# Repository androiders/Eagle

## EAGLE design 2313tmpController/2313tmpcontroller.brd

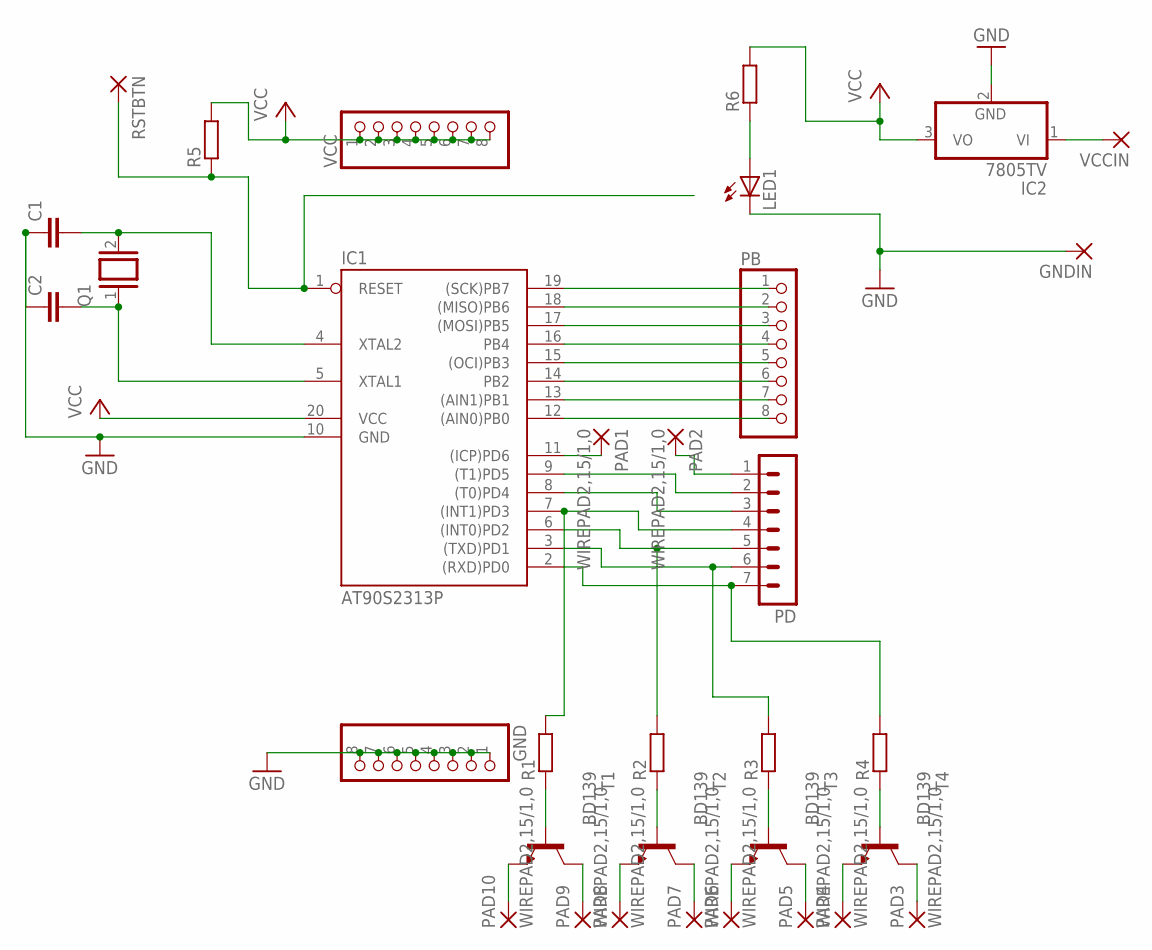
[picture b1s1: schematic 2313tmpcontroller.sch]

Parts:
C1, C2: C2,5-3; C2.5-3
GND: PINHD-1X8; 1X08
GNDIN: 2,54/0,8
IC1: AT90S2313P; DIL20
IC2: 7805TV; TO220V
LED1: LEDB153; Q62902-B153
PAD1, PAD2, PAD3, PAD4, PAD5, PAD6, PAD7, PAD8, PAD9, PAD10: WIREPAD2,15/1,0; 2,15/1,0
PB: PINHD-1X8; 1X08
PD: MA07-1
Q1: XTAL/S; QS
R1, R2, R3, R4, R5, R6: R-EU_0207/7; 0207/7
RSTBTN: 2,54/0,8
T1, T2, T3, T4: BD139; TO126
VCC: PINHD-1X8; 1X08
VCCIN: 2,54/0,8

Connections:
GND: C1.1, C2.1, GND.1, GND.2, GND.3, GND.4, GND.5, GND.6, GND.7, GND.8, GNDIN.1, IC1.10 (GND), IC2.2 (GND), LED1.K (C)
unnamed: IC1.12 ((AIN0)PB0), PB.8
unnamed: IC1.13 ((AIN1)PB1), PB.7
unnamed: IC1.14 (PB2), PB.6
unnamed: IC1.15 ((OCI)PB3), PB.5
unnamed: IC1.16 (PB4), PB.4
unnamed: IC1.17 ((MOSI)PB5), PB.3
unnamed: IC1.18 ((MISO)PB6), PB.2
unnamed: IC1.19 ((SCK)PB7), PB.1
unnamed: IC1.2 ((RXD)PD0), PD.7, R4.2
unnamed: IC1.3 ((TXD)PD1), PD.6, R3.2
unnamed: IC1.6 ((INT0)PD2), PD.5, R2.2
unnamed: IC1.7 ((INT1)PD3), PD.4, R1.2
unnamed: IC1.8 ((T0)PD4), PD.3
unnamed: IC1.9 ((T1)PD5), PD.2
unnamed: IC1.11 ((ICP)PD6), PAD1.1
unnamed: C2.2, IC1.5 (XTAL1), Q1.1
unnamed: C1.2, IC1.4 (XTAL2), Q1.2
unnamed: R1.1, T1.3 (B)
unnamed: IC1.1 (RESET), R5.1, RSTBTN.1
unnamed: R2.1, T2.3 (B)
unnamed: R3.1, T3.3 (B)
unnamed: R4.1, T4.3 (B)
unnamed: PAD10.1, T1.1 (E)
unnamed: PAD9.1, T1.2 (C)
unnamed: PAD8.1, T2.1 (E)
unnamed: PAD7.1, T2.2 (C)
unnamed: PAD6.1, T3.1 (E)
unnamed: PAD5.1, T3.2 (C)
unnamed: PAD4.1, T4.1 (E)
unnamed: PAD3.1, T4.2 (C)
unnamed: PAD2.1, PD.1
unnamed: LED1.A, R6.1
unnamed: IC2.1 (VI), VCCIN.1
VCC: IC1.20 (VCC), IC2.3 (VO), R5.2, R6.2, VCC.1, VCC.2, VCC.3, VCC.4, VCC.5, VCC.6, VCC.7, VCC.8

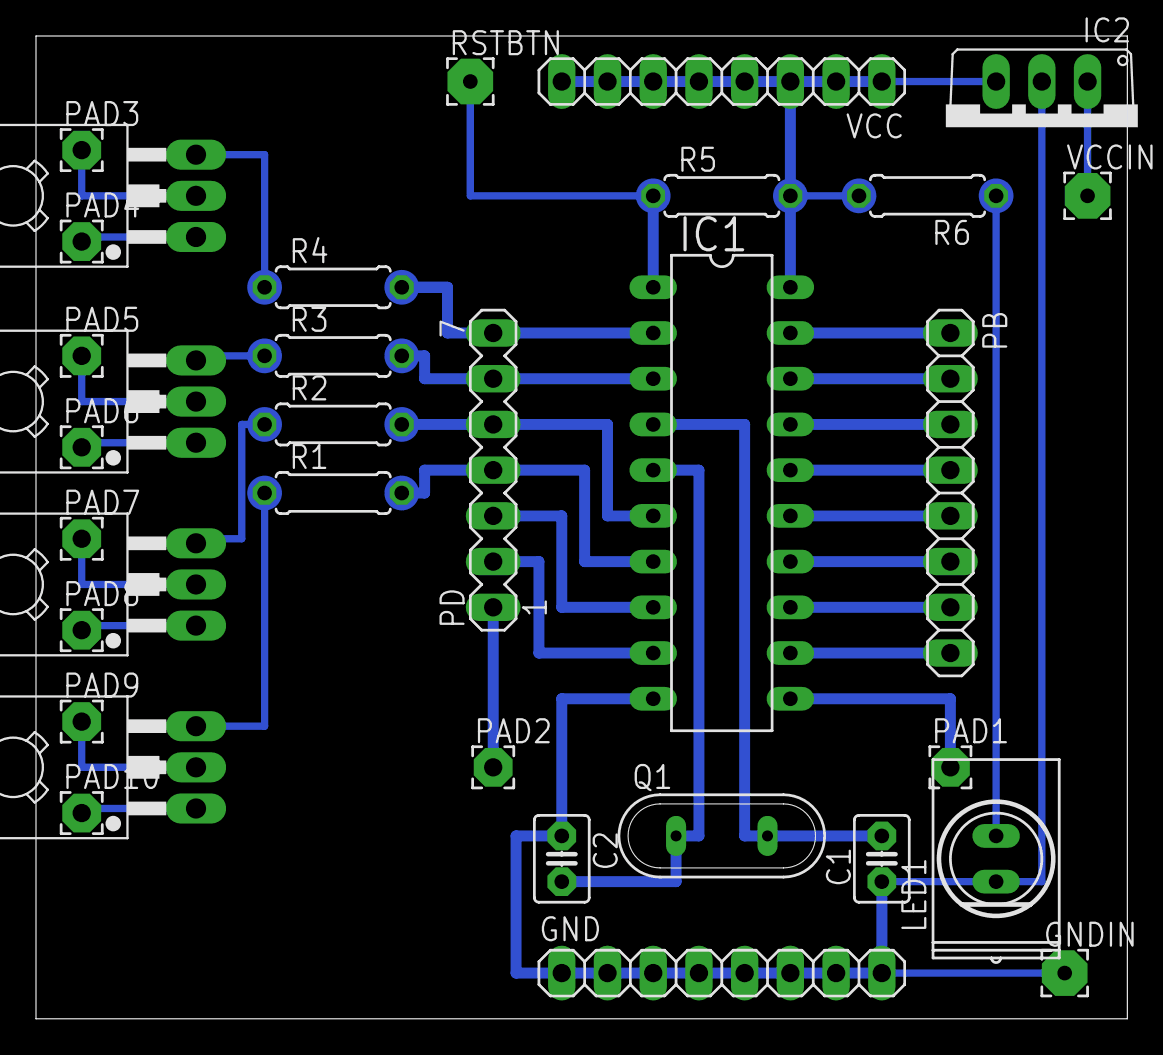
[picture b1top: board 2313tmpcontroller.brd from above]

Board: 2 copper layers, 60.6 x 54.6 mm, 33 parts (0 on the bottom side), 35 nets.

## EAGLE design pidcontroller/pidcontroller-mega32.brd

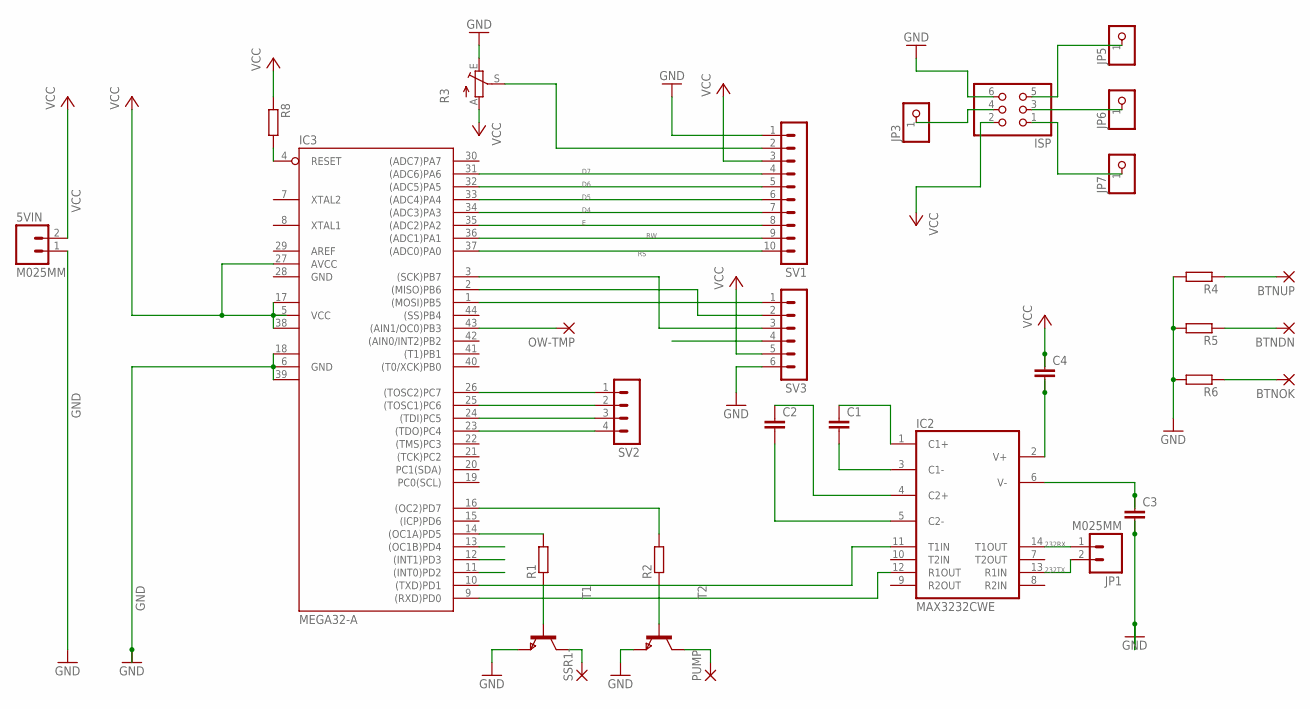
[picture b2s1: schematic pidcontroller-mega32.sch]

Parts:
5VIN: M025MM; SCREWTERMINAL-5MM-2
BTNDN: 2,15/1,0
BTNOK: 2,15/1,0
BTNUP: 2,15/1,0
C1, C2, C3, C4: C-EUC1206; C1206
IC2: MAX3232CWE; SO16L
IC3: MEGA32-A; TQFP44
ISP: PINHD-2X3; 2X03
JP1: M025MM; SCREWTERMINAL-5MM-2
JP3, JP5, JP6, JP7: PINHD-1X1; 1X01
OW-TMP: 2,15/1,0
PUMP: 2,15/1,0
R1, R2, R4, R5, R6, R8: R-EU_R0603; R0603
R3: TRIM_EU-LI10; LI10
SSR1-: 2,15/1,0
SV1: MA10-1
SV2: MA04-1
SV3: MA06-1
T1, T2: NPNSOT23; SOT-23

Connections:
232RX: IC2.14 (T1OUT), JP1.1
232TX: IC2.13 (R1IN), JP1.2
BTNDN: BTNDN.1, IC3.12 ((INT1)PD3), R5.1
BTNOK: BTNOK.1, IC3.11 ((INT0)PD2), R6.1
BTNUP: BTNUP.1, IC3.13 ((OC1B)PD4), R4.1
D4: IC3.34 ((ADC3)PA3), SV1.7
D5: IC3.33 ((ADC4)PA4), SV1.6
D6: IC3.32 ((ADC5)PA5), SV1.5
D7: IC3.31 ((ADC6)PA6), SV1.4
E: IC3.35 ((ADC2)PA2), SV1.8
GND: 5VIN.1, C3.2, IC2.15 (GND), IC3.6 (GND), IC3.18 (GND1), IC3.28 (GND), IC3.39 (GND2), ISP.6, R3.E, R4.2, R5.2, R6.2, SV1.1, SV3.6, T1.2 (E), T2.2 (E)
unnamed: IC3.3 ((SCK)PB7), SV3.3
unnamed: R1.1, T1.3 (B)
unnamed: R2.1, T2.3 (B)
unnamed: IC3.14 ((OC1A)PD5), R1.2
unnamed: C2.2, IC2.5 (C2-)
unnamed: C2.1, IC2.4 (C2+)
unnamed: C1.2, IC2.3 (C1-)
unnamed: C1.1, IC2.1 (C1+)
unnamed: C4.2, IC2.2 (V+)
unnamed: IC3.16 ((OC2)PD7), R2.2
unnamed: C3.1, IC2.6 (V-)
unnamed: IC2.11 (T1IN), IC3.10 ((TXD)PD1)
unnamed: IC2.12 (R1OUT), IC3.9 ((RXD)PD0)
unnamed: IC3.1 ((MOSI)PB5), SV3.1
unnamed: IC3.2 ((MISO)PB6), SV3.2
unnamed: IC3.43 ((AIN1/OC0)PB3), OW-TMP.1
unnamed: R3.S, SV1.2
unnamed: ISP.4, JP3.1
unnamed: SSR1-.1, T1.1 (C)
unnamed: PUMP.1, T2.1 (C)
unnamed: ISP.1, JP7.1
unnamed: ISP.3, JP6.1
unnamed: ISP.5, JP5.1
unnamed: IC3.26 ((TOSC2)PC7), SV2.1
unnamed: IC3.25 ((TOSC1)PC6), SV2.2
unnamed: IC3.24 ((TDI)PC5), SV2.3
unnamed: IC3.23 ((TDO)PC4), SV2.4
RESET: IC3.4 (RESET), R8.2, SV3.4
RS: IC3.37 ((ADC0)PA0), SV1.10
RW: IC3.36 ((ADC1)PA1), SV1.9
VCC: 5VIN.2, C4.1, IC2.16 (VCC), IC3.5 (VCC), IC3.17 (VCC1), IC3.27 (AVCC), IC3.38 (VCC2), ISP.2, R3.A, R8.1, SV1.3, SV3.5

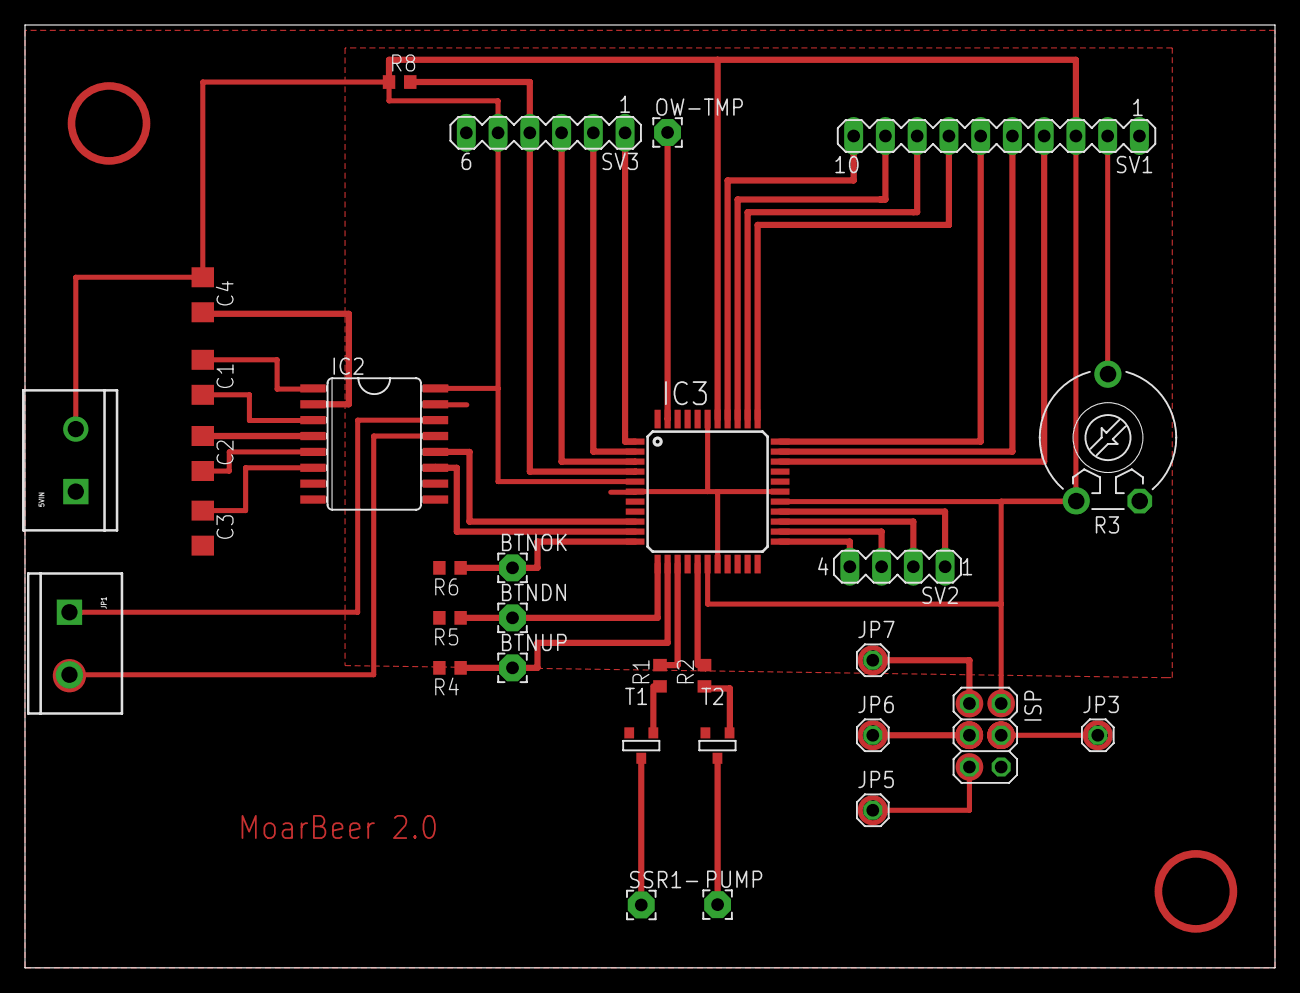
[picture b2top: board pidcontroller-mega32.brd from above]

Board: 2 copper layers, 100.0 x 75.4 mm, 31 parts (0 on the bottom side), 42 nets.

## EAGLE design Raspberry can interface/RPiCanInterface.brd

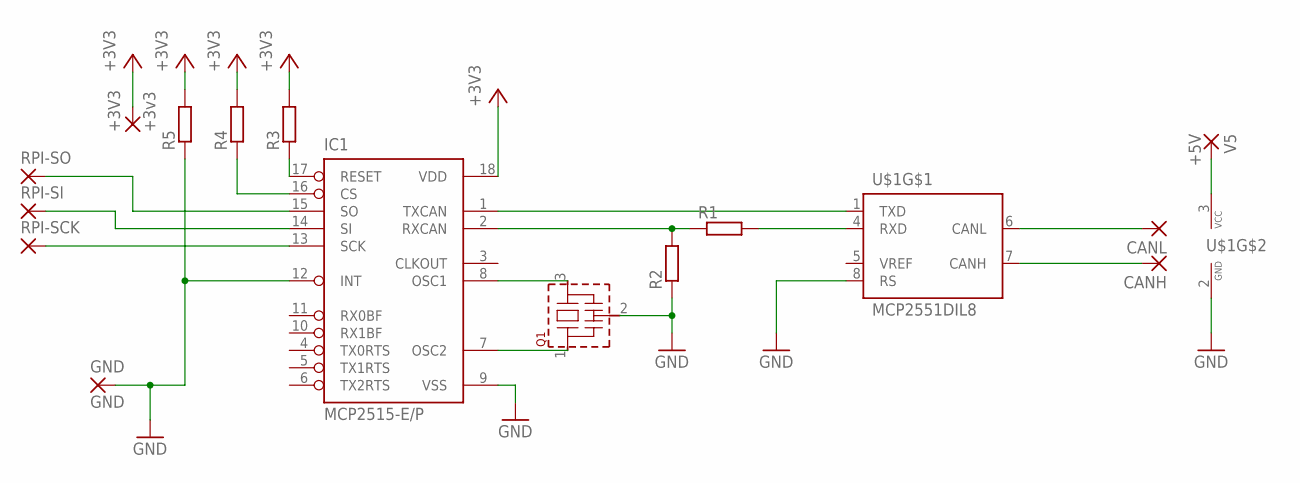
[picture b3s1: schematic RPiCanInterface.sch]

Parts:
+3V3: +3v3; 1,6/0,8
CANH: 1,6/0,8
CANL: 1,6/0,8
GND: GND; 1,6/0,8
IC1: MCP2515-E/P; DIL18
Q1: CSTLA_T
R1, R2, R3, R4, R5: R-EU_0207/7; 0207/7
RPI-SCK: 1,6/0,8
RPI-SI: 1,6/0,8
RPI-SO: 1,6/0,8
U$1: MCP2551DIL8; DIL08
V5: +5V; 1,6/0,8

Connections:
GND: GND.1, IC1.9 (VSS), IC1.12 (INT), Q1.2 (VSS), R2.1, R5.1, U$1.2 (GND), U$1.8 (RS)
unnamed: IC1.1 (TXCAN), U$1.1 (TXD)
unnamed: IC1.2 (RXCAN), R1.1, R2.2
unnamed: R1.2, U$1.4 (RXD)
unnamed: IC1.7 (OSC2), Q1.1
unnamed: IC1.8 (OSC1), Q1.3
unnamed: CANL.1, U$1.6 (CANL)
unnamed: CANH.1, U$1.7 (CANH)
unnamed: IC1.17 (RESET), R3.1
unnamed: IC1.16 (CS), R4.1
unnamed: IC1.15 (SO), RPI-SO.1
unnamed: IC1.14 (SI), RPI-SI.1
unnamed: IC1.13 (SCK), RPI-SCK.1
unnamed: U$1.3 (VCC), V5.1
VCC: +3V3.1, IC1.18 (VDD), R3.2, R4.2, R5.2

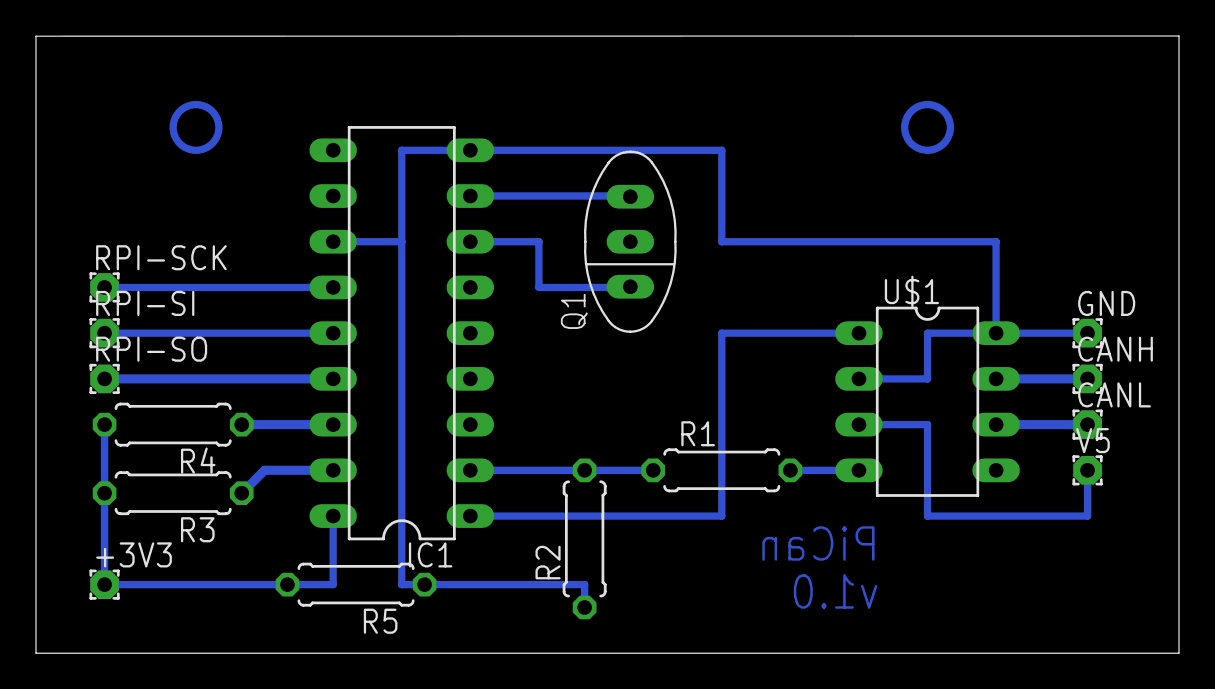
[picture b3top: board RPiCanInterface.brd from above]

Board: 2 copper layers, 63.5 x 34.3 mm, 16 parts (0 on the bottom side), 15 nets.

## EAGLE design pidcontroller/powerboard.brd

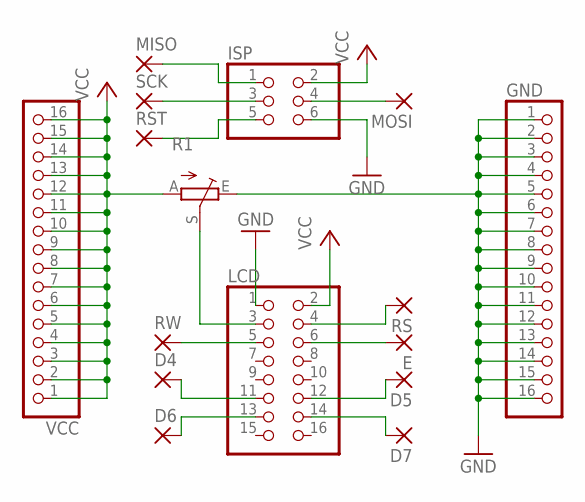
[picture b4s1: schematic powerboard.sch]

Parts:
D4, D5, D6, D7: 2,54/1,1
E: 2,54/1,1
GND: PINHD-1X16; 1X16
ISP: PINHD-2X3; 2X03
LCD: PINHD-2X8; 2X08
MISO: 2,54/1,1
MOSI: 2,54/1,1
R1: TRIM_EU-LI10; LI10
RS: 2,54/1,1
RST: 2,54/1,1
RW: 2,54/1,1
SCK: 2,54/1,1
VCC: PINHD-1X16; 1X16

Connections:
GND: GND.1, GND.2, GND.3, GND.4, GND.5, GND.6, GND.7, GND.8, GND.9, GND.10, GND.11, GND.12, GND.13, GND.14, GND.15, GND.16, ISP.6, LCD.1, R1.E
unnamed: LCD.4, RS.1
unnamed: LCD.5, RW.1
unnamed: ISP.1, MISO.1
unnamed: ISP.3, SCK.1
unnamed: ISP.5, RST.1
unnamed: ISP.4, MOSI.1
unnamed: E.1, LCD.6
unnamed: D4.1, LCD.11
unnamed: D5.1, LCD.12
unnamed: D6.1, LCD.13
unnamed: D7.1, LCD.14
unnamed: LCD.3, R1.S
VCC: ISP.2, LCD.2, R1.A, VCC.1, VCC.2, VCC.3, VCC.4, VCC.5, VCC.6, VCC.7, VCC.8, VCC.9, VCC.10, VCC.11, VCC.12, VCC.13, VCC.14, VCC.15, VCC.16

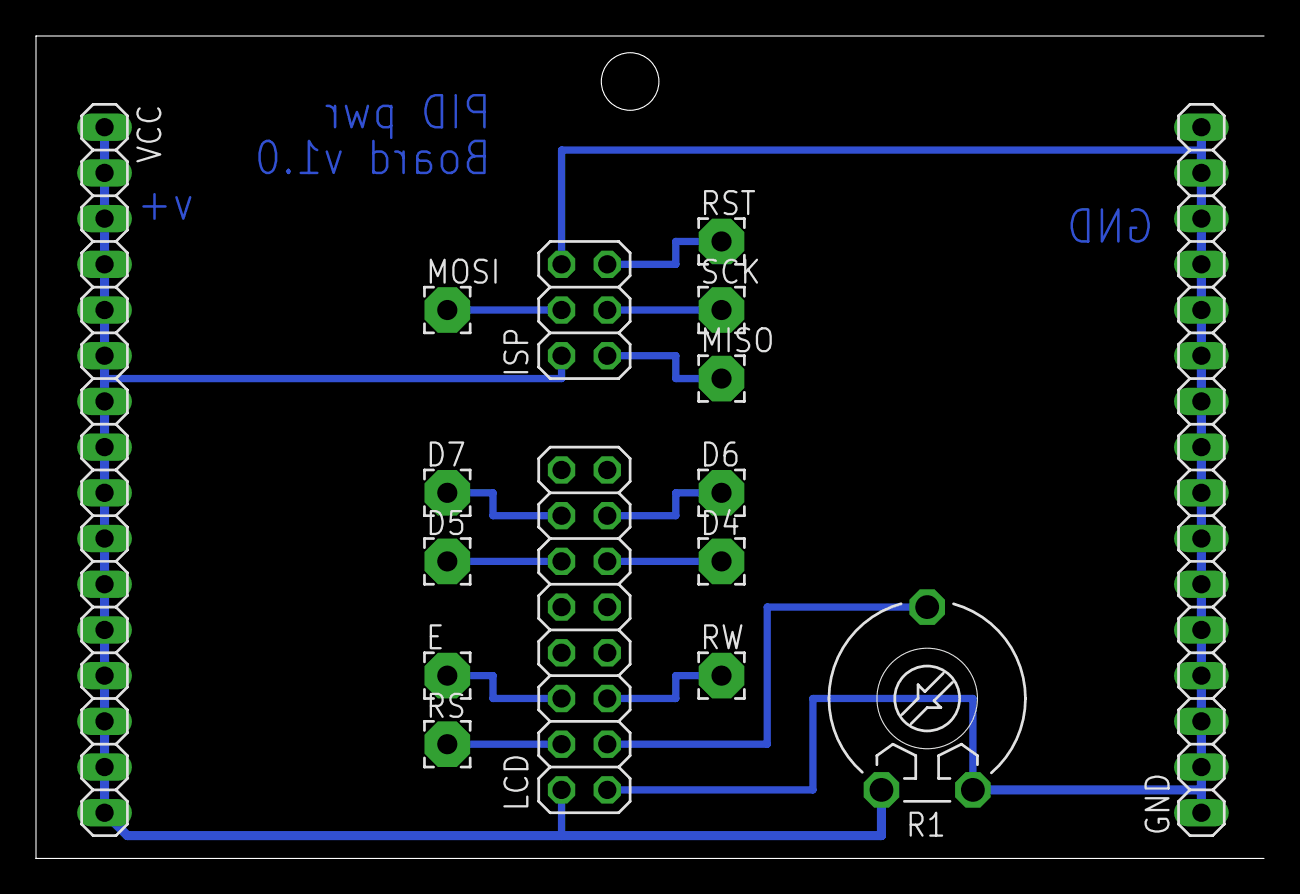
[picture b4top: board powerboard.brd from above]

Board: 2 copper layers, 68.2 x 45.7 mm, 16 parts (0 on the bottom side), 14 nets.

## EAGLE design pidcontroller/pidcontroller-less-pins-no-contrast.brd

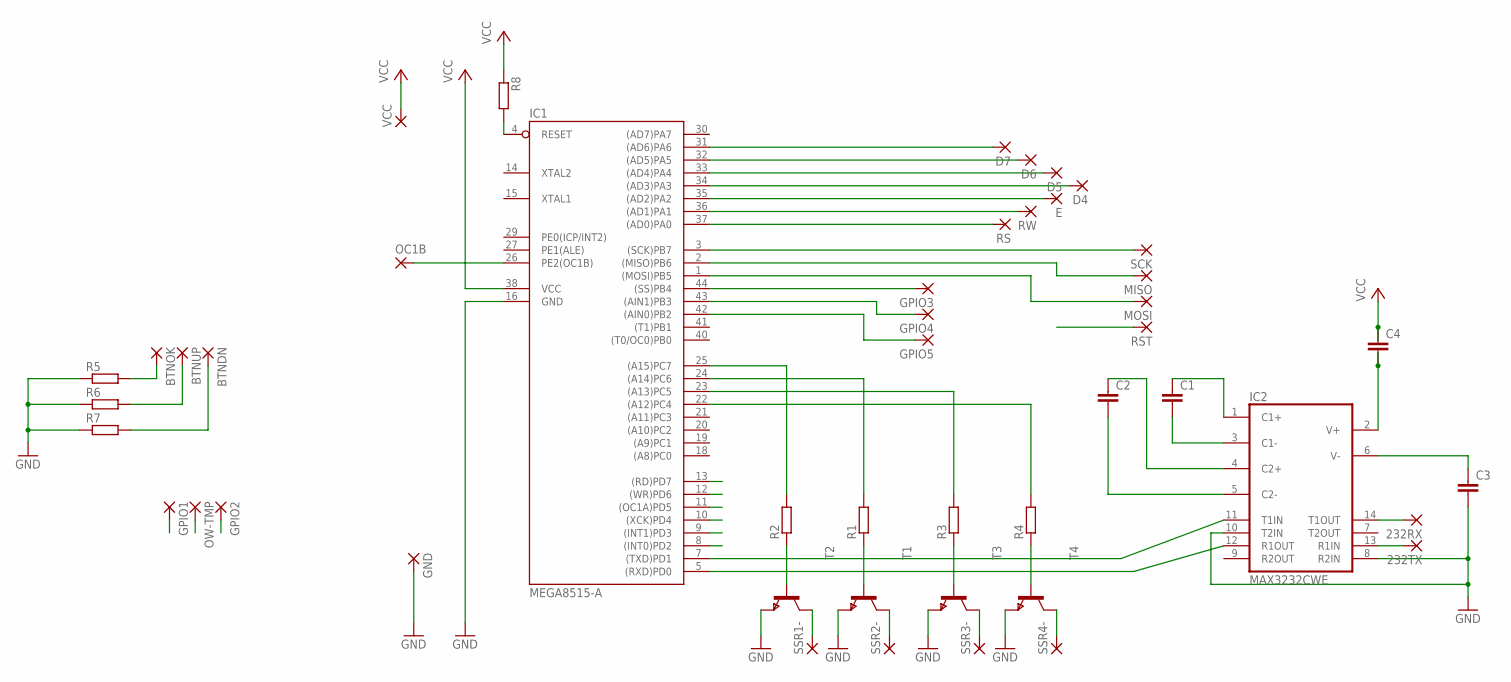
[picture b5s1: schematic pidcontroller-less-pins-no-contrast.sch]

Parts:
232RX, 232TX: 2,54/1,0
BTNDN: 2,15/1,0
BTNOK: 2,15/1,0
BTNUP: 2,15/1,0
C1, C2, C3, C4: C-EUC1206; C1206
D4, D5, D6, D7: 2,54/1,0
E: 2,54/1,0
GND: 2,54/1,0
GPIO1, GPIO2: 2,15/1,0
GPIO3, GPIO4, GPIO5: 2,54/1,0
IC1: MEGA8515-A; TQFP44
IC2: MAX3232CWE; SO16L
MISO: 2,54/1,0
MOSI: 2,54/1,0
OC1B: 2,54/1,0
OW-TMP: 2,15/1,0
R1, R2, R3, R4, R5, R6, R7, R8: R-EU_R0603; R0603
RS: 2,54/1,0
RST: 2,54/1,0
RW: 2,54/1,0
SCK: 2,54/1,0
SSR1-, SSR2-, SSR3-, SSR4-: 2,15/1,0
T1, T2, T3, T4: NPNSOT23; SOT-23
VCC: 2,54/1,0

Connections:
1: D6.1, IC1.32 ((AD5)PA5)
GND: C3.2, GND.1, IC1.16 (GND), IC2.8 (R2IN), IC2.10 (T2IN), IC2.15 (GND), R5.1, R6.1, R7.1, T1.2 (E), T2.2 (E), T3.2 (E), T4.2 (E)
unnamed: IC1.3 ((SCK)PB7), SCK.1
unnamed: R1.1, T1.3 (B)
unnamed: R2.1, T2.3 (B)
unnamed: IC1.24 ((A14)PC6), R1.2
unnamed: C2.2, IC2.5 (C2-)
unnamed: C2.1, IC2.4 (C2+)
unnamed: C1.2, IC2.3 (C1-)
unnamed: C1.1, IC2.1 (C1+)
unnamed: C4.2, IC2.2 (V+)
unnamed: IC1.25 ((A15)PC7), R2.2
unnamed: C3.1, IC2.6 (V-)
unnamed: IC1.7 ((TXD)PD1), IC2.11 (T1IN)
unnamed: IC1.5 ((RXD)PD0), IC2.12 (R1OUT)
unnamed: IC1.2 ((MISO)PB6), MISO.1
unnamed: IC1.1 ((MOSI)PB5), MOSI.1
unnamed: IC1.37 ((AD0)PA0), RS.1
unnamed: IC1.36 ((AD1)PA1), RW.1
unnamed: E.1, IC1.35 ((AD2)PA2)
unnamed: D4.1, IC1.34 ((AD3)PA3)
unnamed: D5.1, IC1.33 ((AD4)PA4)
unnamed: GPIO5.1, IC1.42 ((AIN0)PB2)
unnamed: D7.1, IC1.31 ((AD6)PA6)
unnamed: SSR2-.1, T1.1 (C)
unnamed: SSR1-.1, T2.1 (C)
unnamed: 232RX.1, IC2.14 (T1OUT)
unnamed: 232TX.1, IC2.13 (R1IN)
unnamed: SSR3-.1, T3.1 (C)
unnamed: SSR4-.1, T4.1 (C)
unnamed: R3.1, T3.3 (B)
unnamed: R4.1, T4.3 (B)
unnamed: IC1.23 ((A13)PC5), R3.2
unnamed: IC1.22 ((A12)PC4), R4.2
unnamed: GPIO4.1, IC1.43 ((AIN1)PB3)
unnamed: GPIO3.1, IC1.44 ((SS)PB4)
unnamed: IC1.26 (PE2(OC1B)), OC1B.1
PD2: GPIO1.1, IC1.8 ((INT0)PD2)
PD3: BTNOK.1, IC1.9 ((INT1)PD3), R5.2
PD4: GPIO2.1, IC1.10 ((XCK)PD4)
PD5: BTNUP.1, IC1.11 ((OC1A)PD5), R6.2
PD6: IC1.12 ((WR)PD6), OW-TMP.1
PD7: BTNDN.1, IC1.13 ((RD)PD7), R7.2
RESET: IC1.4 (RESET), R8.2, RST.1
VCC: C4.1, IC1.38 (VCC), IC2.16 (VCC), R8.1, VCC.1

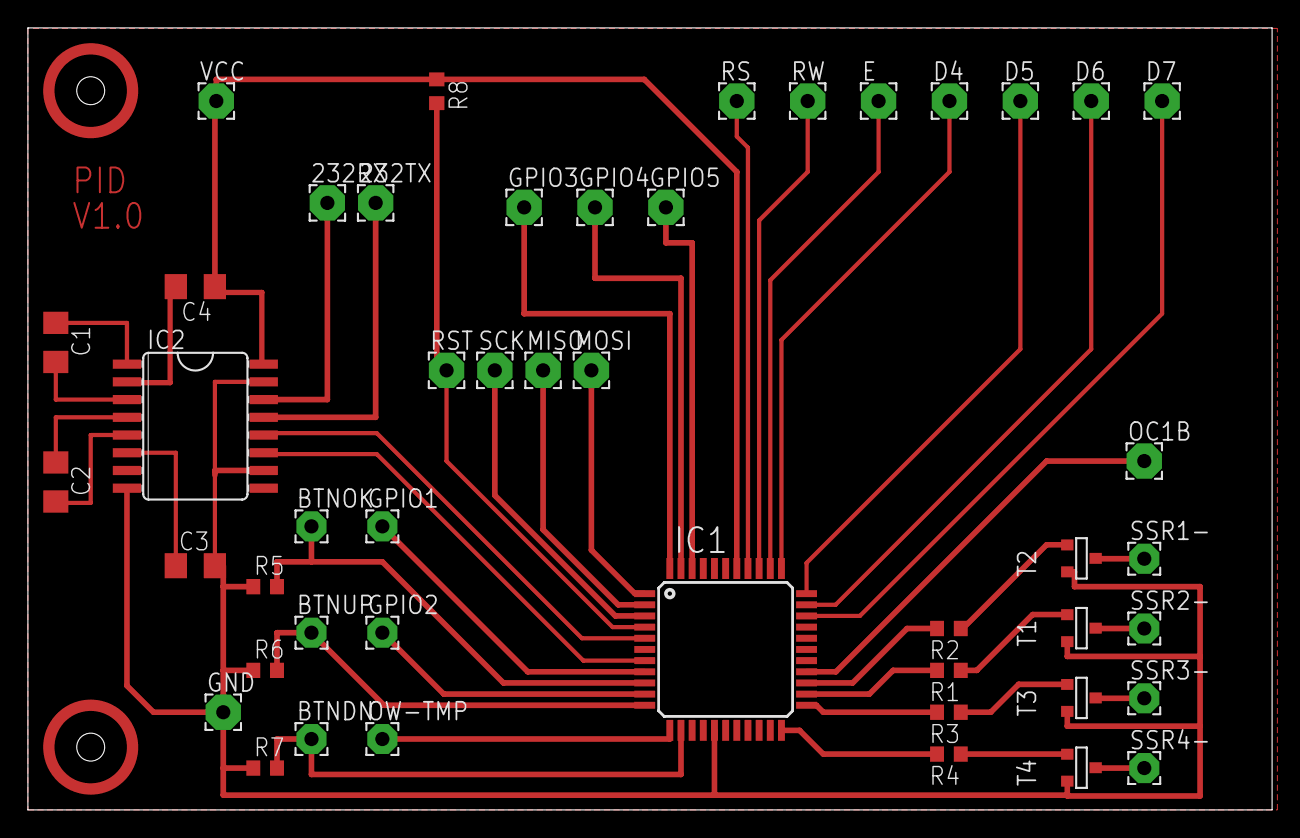
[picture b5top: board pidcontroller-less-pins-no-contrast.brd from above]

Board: 2 copper layers, 89.2 x 56.0 mm, 47 parts (0 on the bottom side), 45 nets.

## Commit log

2013-12-12 added eagle files
2013-12-12 updated eagle files
2013-12-19 added sch and brd for rpi can interface
2013-12-19 changed can interface board
2013-12-19 updated pi can board
2013-12-19 asdf
2013-12-19 modified blinky
2013-12-19 asdfad
2013-12-19 removed some files
2013-12-19 fixed error on pican board
2014-07-02 new version of board, correct chip ;)
2014-07-03 more work!
2014-07-03 prettified board
2014-07-03 adfasdf
2014-07-03 updated schematic and board
2014-07-04 cleanded up
2014-07-04 added gndplane
2014-07-04 nicer board nicer board
2014-08-17 updated board for PID
2014-08-18 updated board
2014-08-21 thicker lines
2014-08-22 changed stuff
2014-08-22 fixed wire
2014-08-24 asdfjh
2014-08-26 updated isp
2014-08-27 added extra pins
2014-08-28 more changes
2014-09-16 new controller board based on 2313 and changes to pidcontroller eagle file
2014-09-16 fixed some pads
2014-09-16 added 7805

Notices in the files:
parts and their libraries:
SparkFun-Connectors: Licensing: Creative Commons ShareAlike 4.0 International - https://creativecommons.org/licenses/by-sa/4.0
